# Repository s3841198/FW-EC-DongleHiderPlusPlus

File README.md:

# DongleHider++ Framework Laptop Expansion Card

This is a fork of LeoDJ's dongle hider plus, it is a slight refinement of the design fitting it into a pcb that is compatible with a stock Framework USB C expansion card.

Simply (permanently) mount the dongle inside the card and still have an USB A port available!  

There even is room and solder pads for an additional dongle. Your imagination (and physics) are the only limits!

See LeoDJ's [thread on Mastodon about the build process etc](https://chaos.social/@LeoDJ/112040053271880119).

<p float="left" style="display: flex; flex-wrap: wrap; align-items: center;">
  &nbsp;
  
</p>

## Compatibility Notes

The expansion card was only tested on **Windows** and **AMD** Framework **13 and 16** laptops as of right now. There the following behaviour has been observed:
- With only a dongle active, the CH334 hub IC draws around 20mA. (In addition to the ~25mA of the Unifying dongle)
  - When nothing is connected to the hub, it goes to sleep and draws <1mA. (But this is seldomly the case with a dongle permanently attached to it :P )
- Despite earlier fears, the USB 3 "route-around-2.0-hub" topology doesn't seem to cause problems in the wild, except:
- When connected to a **USB4 capable expansion card slot** and an external **USB 3 device** is plugged in, the **internal dongle stops working**, but is still displayed as connected in Windows.
  - As soon as the USB 3 device gets unplugged, the internal dongle immediately begins to work again (probably without a re-enumeration).
  - USB 2 devices seem to work without a problem for the most part, although one of the tested USB thumb drives took a few re-plugs until it enumerated.
  - This behaviour is not seen on the other non-USB4-capable expansion card slots, there USB 3 devices work great alongside the internal dongle

It's currently unclear what the behaviour would be under Linux or on Intel laptops. <sup>[You can help expand this]</sup>

### Dongles

Please note that there may be mechanical differences between the original DongleHiderPlus and this pcb, I would reccomend 3D printing the pcb outline and checking the fit of your dongle.

The Unifying dongles can be disassembled pretty easily:
|||
|---|---|
|  | **Gen 1:** <br>Carefully break off the plastic from the metal part using a pair of pliers. <br>(Can be glued back together, if needed)|
|  | **Gen 2:** <br>Slide flat screwdriver (or similar) between the metal and the orange plastic of the front of the USB a plug and carefully pry open the metal shell until it slides off. <br>[Youtube video](https://www.youtube.com/watch?v=NB5uVCrXxT8) |

## PCB
- [View the latest schematic and board view]([https://kicanvas.org/?github=https%3A%2F%2Fgithub.com%2FLeoDJ%2FFW-EC-DongleHiderPlus%2Ftree%2Fmain%2FDongleHiderPlus_PCB](https://kicanvas.org/?github=https://github.com/s3841198/FW-EC-DongleHiderPlusPlus/blob/main/FrameworkDongleHiderRetrofit.kicad_pcb)) thanks to KiCanvas.
- I've ordered the PCB and assembled it myself, but it should be able to be mostly assembled by PCBA services (like JLCPCB) too. The Gerber/BOM/CPL files are provided in the [PCB/jlcpcb/production_files/](FW-EC-DongleHiderPlusPlus/tree/main/jlcpcb/production_files) folder.

## Mechanical Design

- The pcb is designed to be a drop in replacement for a stock Framework USB C expansion card, it uses the original screws and doesn't require any modifications to be made to the stock housing.

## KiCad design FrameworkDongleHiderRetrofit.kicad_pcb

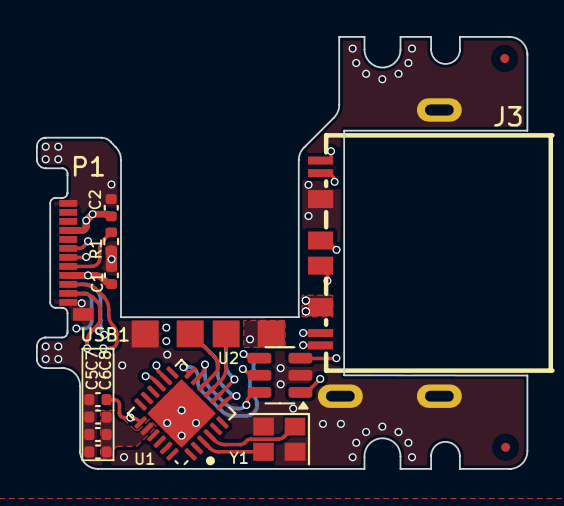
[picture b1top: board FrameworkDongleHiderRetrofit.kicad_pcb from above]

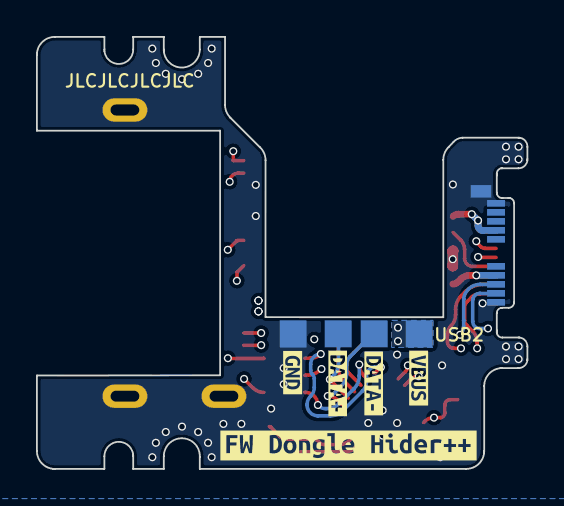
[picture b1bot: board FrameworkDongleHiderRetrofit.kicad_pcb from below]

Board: 4 copper layers, 27.3 x 24.0 mm, 19 parts (6 on the bottom side), 20 nets.

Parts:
C1, C2: 10n; C_0402_1005Metric
C5, C8: 1u; C_0402_1005Metric
C6: 10u; C_0402_1005Metric
C7: 100n; C_0402_1005Metric
J3: USB3_A; USB-A-SMD_HC-USB3.0-C345-P
P1: USB_C_Plug; USB_C_Plug_Molex_105444
R1: 5k1; R_0402_1005Metric
U1: CH334F; QFN-24-1EP_4x4mm_P0.5mm_EP2.7x2.7mm
U2: USBLC6-2SC6; SOT-23-6
USB1, USB2: USB Dongle; USB_SolderPads
Y1: 12MHz; Crystal_SMD_2520-4Pin_2.5x2.0mm
kibuzzard-67B71C1E: G***; kibuzzard-67B71C1E
kibuzzard-67B71C3E: G***; kibuzzard-67B71C3E
kibuzzard-67B71C39: G***; kibuzzard-67B71C39
kibuzzard-67B71C43: G***; kibuzzard-67B71C43
kibuzzard-67B71FEC: G***; kibuzzard-67B71FEC

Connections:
GND: C1.2, C2.2, C5.2, C6.2, C7.2, C8.2, J3.4 (GND), J3.10 (SHIELD), J3.11 (SHIELD), J3.12 (SHIELD), P1.A1 (GND), P1.A12 (GND), P1.B1 (GND), P1.B12 (GND), P1.S1 (SHIELD), R1.2, U1.25 (GND), U2.2 (GND), USB1.4, USB2.4, Y1.2, Y1.4
unnamed: J3.3 (D+), U2.3 (I/O2)
unnamed: J3.2 (D-), U2.1 (I/O1)
unnamed: P1.A5 (CC), R1.1
unnamed: P1.A6 (D+), U1.15 (DPU+)
unnamed: P1.A7 (D-), U1.14 (DMU-)
unnamed: U1.11 (DM1-), U2.6 (I/O1)
unnamed: U1.9 (DM2-), USB1.2
unnamed: U1.7 (DM3-), USB2.2
unnamed: U1.12 (DP1+), U2.4 (I/O2)
unnamed: U1.10 (DP2+), USB1.3
unnamed: U1.8 (DP3+), USB2.3
unnamed: C6.1, C7.1, C8.1, U1.20 (VDD33)
unnamed: U1.4 (XI), Y1.1
unnamed: U1.3 (XO), Y1.3
RX+: J3.6 (SSRX+), P1.B11 (RX1+)
RX-: J3.5 (SSRX-), P1.B10 (RX1-)
TX+: J3.9 (SSTX+), P1.A2 (TX1+)
TX-: J3.8 (SSTX-), P1.A3 (TX1-)
VBUS: C1.1, C2.1, C5.1, J3.1 (VBUS), P1.A4 (VBUS), P1.A9 (VBUS), P1.B4 (VBUS), P1.B9 (VBUS), U1.19 (V5), U2.5 (VBUS), USB1.1, USB2.1

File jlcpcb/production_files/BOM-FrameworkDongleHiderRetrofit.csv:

Comment,Designator,Footprint,LCSC,Quantity
10n,"C1,C2",C_0402_1005Metric,C15195,2
10u,C6,C_0402_1005Metric,C15525,1
5k1,R1,R_0402_1005Metric,C25905,1
USBLC6-2SC6,U2,SOT-23-6,C2827654,1
12MHz,Y1,Crystal_SMD_2520-4Pin_2.5x2.0mm,C284156,1
100n,C7,C_0402_1005Metric,C307331,1
CH334F,U1,QFN-24-1EP_4x4mm_P0.5mm_EP2.7x2.7mm,C5187527,1
1u,"C5,C8",C_0402_1005Metric,C52923,2
USB_C_Plug,P1,USB_C_Plug_Molex_105444,C561769,1
USB3_A,J3,USB-A-SMD_HC-USB3.0-C345-P,C7501863,1

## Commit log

2025-02-20 Initial Release
